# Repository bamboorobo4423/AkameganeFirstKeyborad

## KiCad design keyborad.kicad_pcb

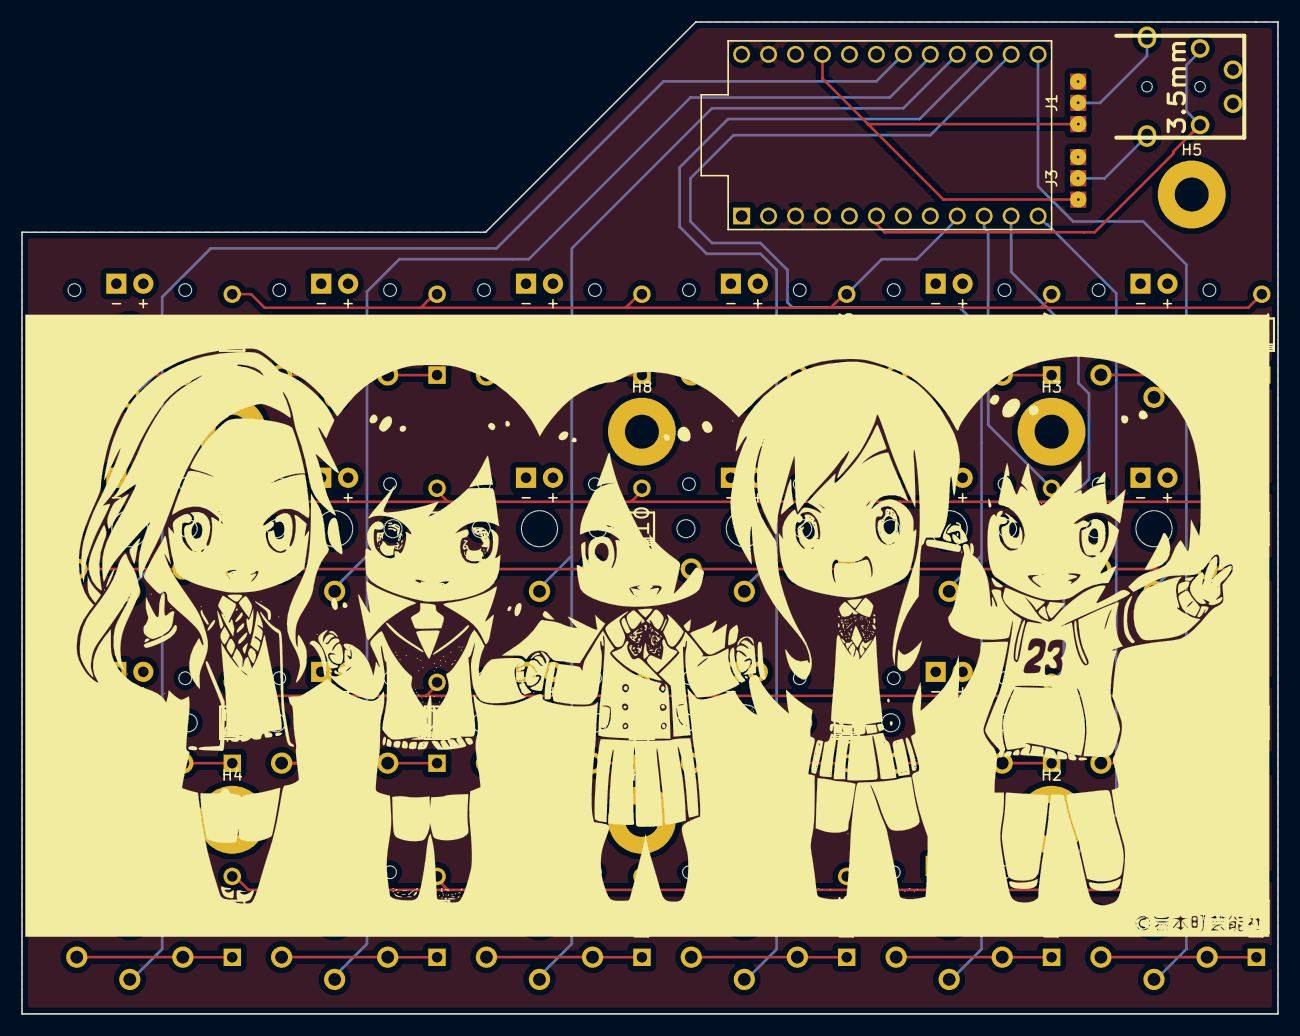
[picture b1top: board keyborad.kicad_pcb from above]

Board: 2 copper layers, 118.4 x 93.5 mm, 59 parts (0 on the bottom side), 39 nets.

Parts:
D1, D2, D3, D4, D5, D6, D7, D8, D9, D10, D11, D12, D13, D14, D15, D16, D17, D18, D19, D20, D21, D22, D23, D24: D; Diode
H2, H3, H4, H5, H6, H7, H8: hole; MountingHole_3.2mm_M3_Pad
J1, J3: 3pin; 3_Pin_Jumper
J2: 6pin; 4pin35mmAudio
SW1, SW2, SW3, SW4, SW5, SW6, SW7, SW8, SW9, SW10, SW11, SW12, SW13, SW14, SW15, SW16, SW17, SW18, SW19, SW20, SW21, SW22, SW23, SW24: SW_DIP_x01; Kailh-PG1350-1u-reversible
U1: ProMicro

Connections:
GND: J1.1, J3.1, U1.3, U1.4, U1.23
unnamed: D1.2, SW1.2
unnamed: D2.2, SW2.2
unnamed: D3.2, SW3.2
unnamed: D4.2, SW4.2
unnamed: D5.2, SW5.2
unnamed: D6.2, SW6.2
unnamed: D7.2, SW7.2
unnamed: D8.2, SW8.2
unnamed: D9.2, SW9.2
unnamed: D10.2, SW10.2
unnamed: D11.2, SW11.2
unnamed: D12.2, SW12.2
unnamed: D13.2, SW13.2
unnamed: D14.2, SW14.2
unnamed: D15.2, SW15.2
unnamed: D16.2, SW16.2
unnamed: D17.2, SW17.2
unnamed: D18.2, SW18.2
unnamed: D19.2, SW19.2
unnamed: D20.2, SW20.2
unnamed: D21.2, SW21.2
unnamed: D22.2, SW22.2
unnamed: D23.2, SW23.2
unnamed: D24.2, SW24.2
unnamed: J1.2, J2.1
unnamed: J2.4, J3.2
VCC: J1.3, J3.3, U1.21
col0: SW1.1, SW2.1, SW3.1, SW4.1, U1.18
col1: SW5.1, SW6.1, SW7.1, SW8.1, U1.17
col2: SW9.1, SW10.1, SW11.1, SW12.1, U1.16
col3: SW13.1, SW14.1, SW15.1, SW16.1, U1.15
col4: SW17.1, SW18.1, SW19.1, SW20.1, U1.14
col5: SW21.1, SW22.1, SW23.1, SW24.1, U1.13
data: J2.2, J2.6, U1.6
row0: D1.1, D5.1, D9.1, D13.1, D17.1, D21.1, U1.9
row1: D2.1, D6.1, D10.1, D14.1, D18.1, D22.1, U1.10
row2: D3.1, D7.1, D11.1, D15.1, D19.1, D23.1, U1.11
row3: D4.1, D8.1, D12.1, D16.1, D20.1, D24.1, U1.12

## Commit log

2018-06-01 最初
    とりあえずアップロード
2018-06-03 ドリルファイルの追加
